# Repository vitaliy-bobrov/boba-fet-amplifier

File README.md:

# Boba Fett Amplifier

Boba Fett Amplifier is a discontinued Boss™ FA-1 FET Amplified in a pedal format. The pedal could be used as a preamp/boost to drive your amp or as a standalone overdrive in the additional mode I added. Overdrive mode enables asymmetrical soft clipping (Tube Screamer style) with 3 LEDs.

The repository contains KiCad source files: schematic, PCB, BOM.

## Schematic

## PCB (3D preview)

## Interactive BOM

👉 [BOM](https://vitaliy-bobrov.github.io/boba-fet-amplifier/)

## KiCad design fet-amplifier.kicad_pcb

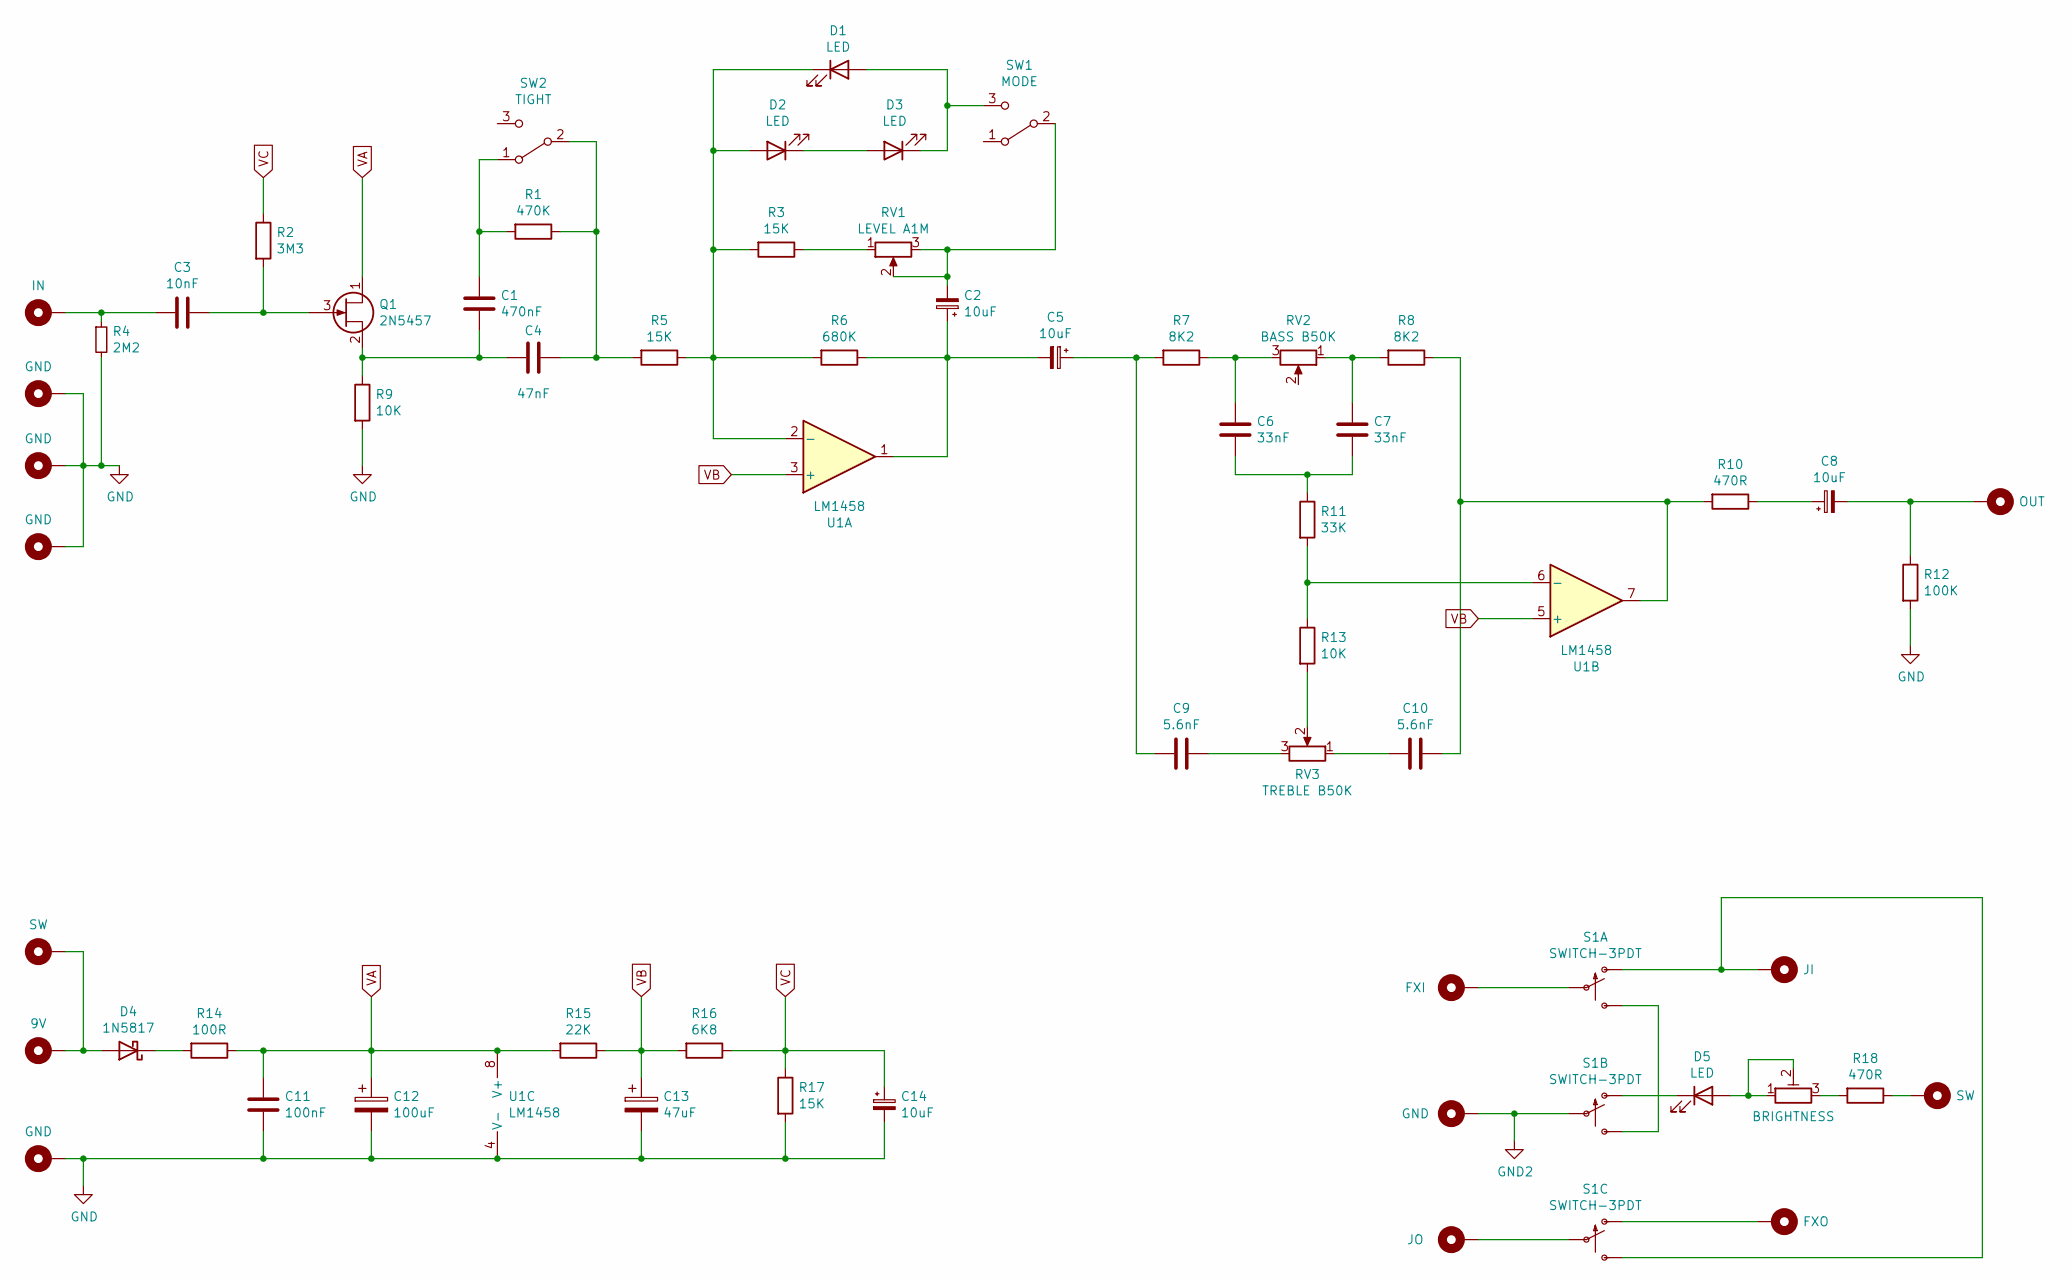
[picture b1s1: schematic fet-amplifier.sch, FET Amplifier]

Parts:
C1: 470nF; 0.2%22.SML
C2, C8: 10uF; 0501
C3: 10nF; 0.2%22.SML
C4: 47nF; 0.2%22.SML
C5, C14: 10uF; 0502
C6, C7: 33nF; 0.2%22.SML
C9, C10: 5.6nF; 0.2%22.SML
C11: 100nF; 0.2%22.SML
C12: 100uF; 0503
C13: 47uF; 0502
D1, D2, D3: LED; 3MM_1
D4: 1N5817; DO41-3
D5: LED; 3MM_IO
H1: IN; PAD1
H2, H3, H5, H11, H12: GND; PAD1
H4: OUT; PAD1
H6, H10: SW; PAD1
H7: JI; PAD1
H8: FXI; PAD1
H9: 9V; PAD1
H13: FXO; PAD1
H14: JO; PAD1
Q1: 2N5457; TO92
R1: 470K; 0.3%22.B
R2: 3M3; 0.3%22.B
R3, R5, R17: 15K; 0.3%22.B
R4: 2M2; 0.2%22
R6: 680K; 0.3%22.B
R7, R8: 8K2; 0.3%22.B
R9, R13: 10K; 0.3%22.B
R10, R18: 470R; 0.3%22.B
R11: 33K; 0.3%22.B
R12: 100K; 0.3%22.B
R14: 100R; 0.3%22.B
R15: 22K; 0.3%22.B
R16: 6K8; 0.3%22.B
RV1: LEVEL A1M; 16MM_B.MOUNT
RV2: BASS B50K; 16MM_B.MOUNT
RV3: TREBLE B50K; 16MM_B.MOUNT
RV4: BRIGHTNESS; TRIM1
S1: SWITCH-3PDT; 3PDT.LUGS.SPF
SW1: MODE; SPDT.LUGS
SW2: TIGHT; SPDT.LUGS
U1: LM1458; DIP08

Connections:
GND: C11.2, C12.2, C13.2, C14.2, H2.1, H3.1, H5.1, H12.1, R4.2, R9.2, R12.2, R17.2, U1.4 (V-)
GND2: H11.1, S1.P$5
unnamed: C1.1, R1.2, SW2.1 (A)
unnamed: C1.2, C4.2, Q1.2 (S), R9.1
unnamed: C2.1, C5.2, R6.1, U1.1
unnamed: C2.2, RV1.2, RV1.3, SW1.2 (B)
unnamed: C3.1, Q1.3 (G), R2.2
unnamed: C3.2, H1.1, R4.1
unnamed: C4.1, R1.1, R5.2, SW2.2 (B)
unnamed: C5.1, C9.2, R7.2
unnamed: C6.1, R7.1, RV2.3
unnamed: C6.2, C7.2, R11.1
unnamed: C7.1, R8.2, RV2.1
unnamed: C8.1, R10.1
unnamed: C8.2, H4.1, R12.1
unnamed: C9.1, RV3.3
unnamed: C10.1, R8.1, R10.2, U1.7
unnamed: C10.2, RV3.1
unnamed: D1.1 (K), D2.2 (A), R3.2, R5.1, R6.2, U1.2 (-)
unnamed: D1.2 (A), D3.1 (K), SW1.3 (C)
unnamed: D2.1 (K), D3.2 (A)
unnamed: D4.1 (K), R14.2
unnamed: D4.2 (A), H6.1, H9.1
unnamed: D5.1 (K), S1.P$4 (O)
unnamed: D5.2 (A), RV4.1, RV4.2
unnamed: H7.1, S1.P$1 (O), S1.P$9 (S)
unnamed: H8.1, S1.P$2
unnamed: H10.1, R18.1
unnamed: H13.1, S1.P$7 (O)
unnamed: H14.1, S1.P$8
unnamed: R3.1, RV1.1
unnamed: R11.2, R13.1, U1.6 (-)
unnamed: R13.2, RV3.2
unnamed: R18.2, RV4.3
unnamed: S1.P$3 (S), S1.P$6 (S)
VA: C11.1, C12.1, Q1.1 (D), R14.1, R15.2, U1.8 (V+)
VB: C13.1, R15.1, R16.2, U1.3 (+), U1.5 (+)
VC: C14.1, R2.1, R16.1, R17.1

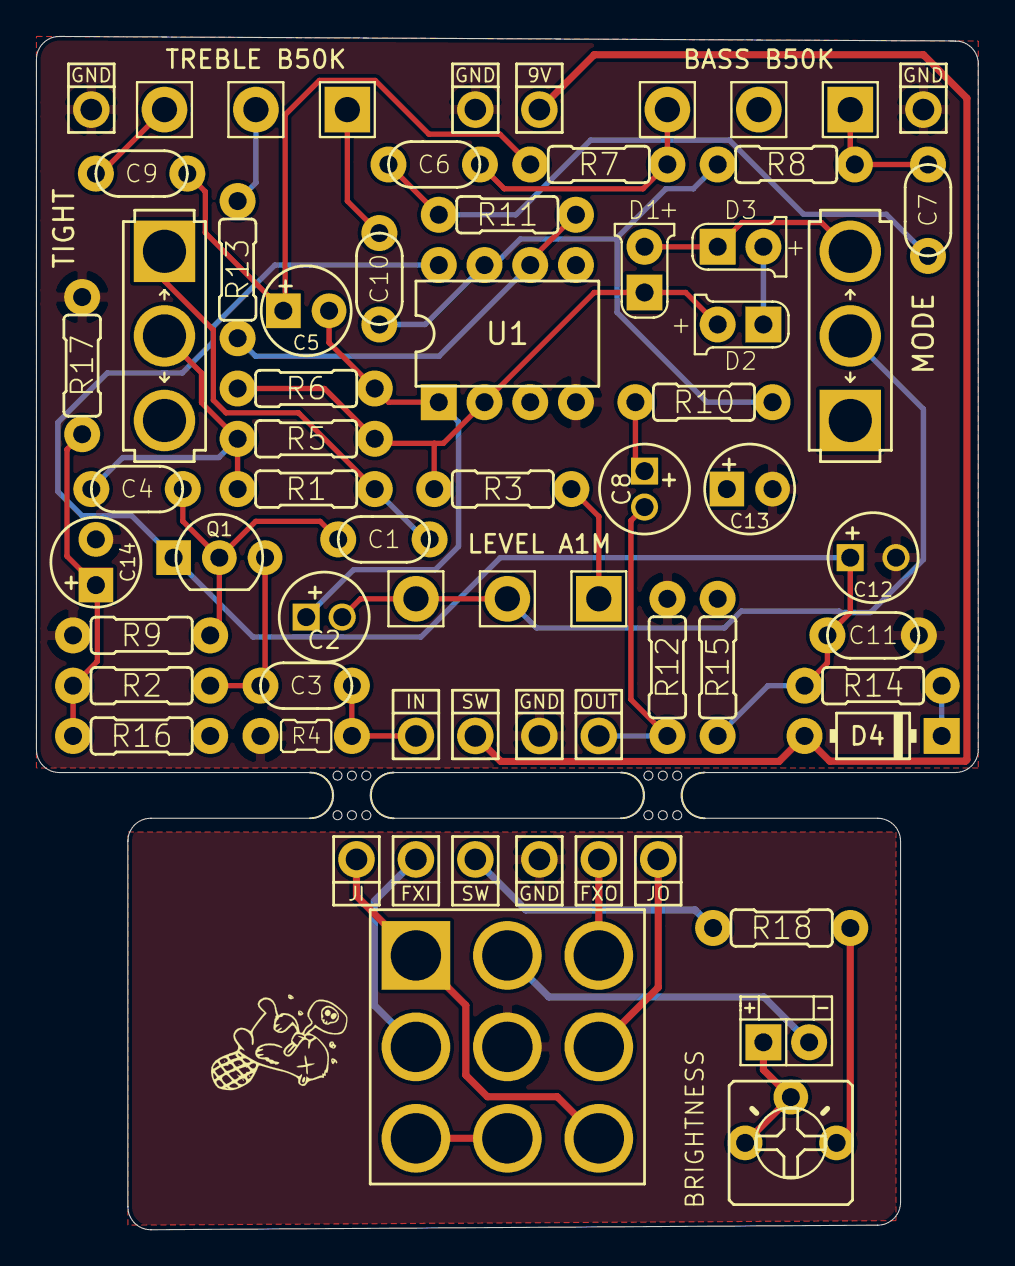
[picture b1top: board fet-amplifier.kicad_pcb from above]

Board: 2 copper layers, 52.3 x 66.3 mm, 62 parts (0 on the bottom side), 38 nets.

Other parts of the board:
mouse-bite-2.54mm-slot, mouse-bite-2.54mm-slot#2: VAL**; mouse-bite-2.54mm-slot

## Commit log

2020-11-30 v1.0
2020-11-30 readme fix
